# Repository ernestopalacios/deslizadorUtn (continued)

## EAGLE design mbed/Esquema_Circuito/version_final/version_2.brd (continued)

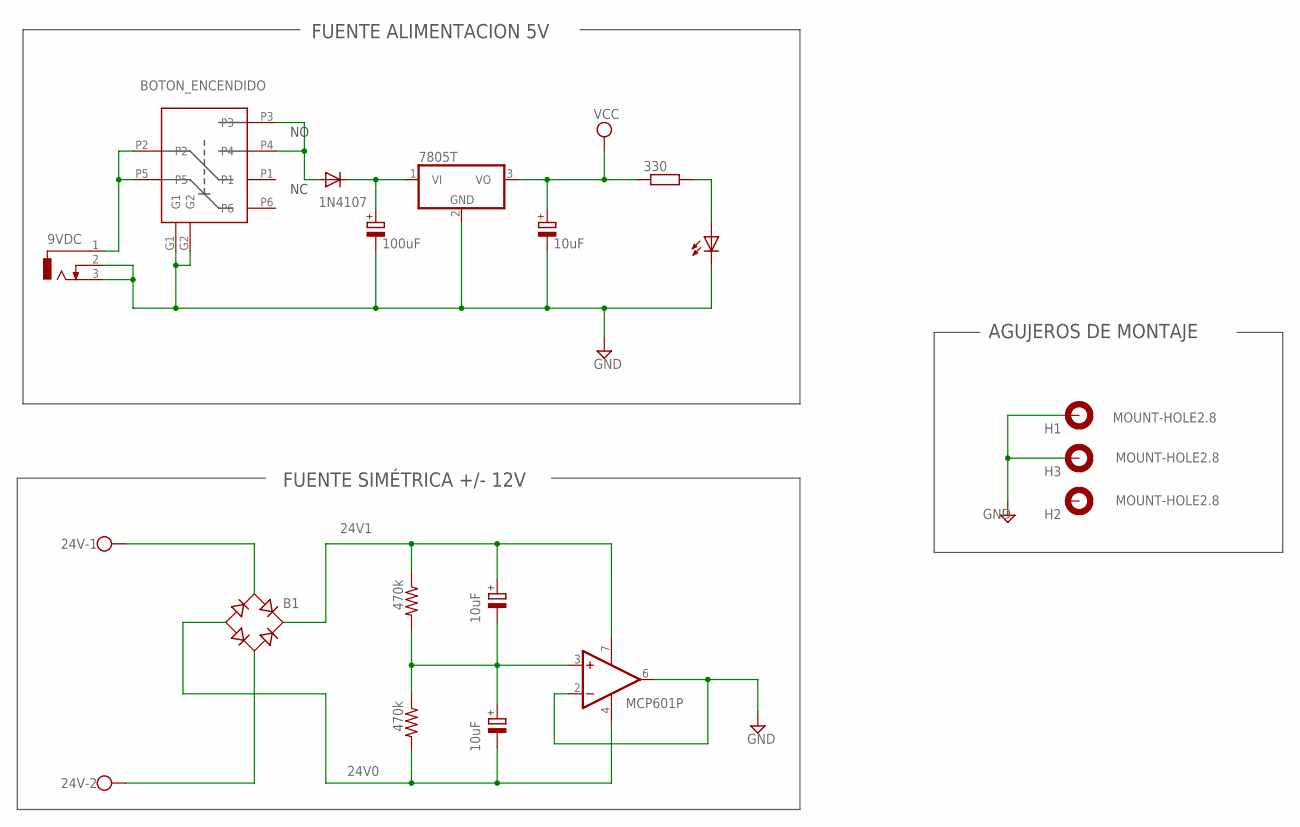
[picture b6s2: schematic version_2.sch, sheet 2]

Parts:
9VDC: DCJ0303
24V: W237-02P; W237-132
B1: RB1A
C1_9V: 100uF; TT5D7
C1_+24, C2_0V, C2_9V: 10uF; TT5D7
D1_INPUT: 1N4107; DO35-10
H1, H2, H3: MOUNT-HOLE2.8; 3,3-PAD
IC2: 7805T; TO220H
IC3: MCP601P; DIL08
ON/OFF: BOTON_ENCENDIDO; BOTON_ENCNEDIDO
POWER: LED3MM
PWR_LED_R: 330; 0204/7
R1_DIV, R2_DIV: 470k; 0207/10

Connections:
24V0: B1.-, C2_0V.-, IC3.4 (V-), R2_DIV.2; also elsewhere on the board
24V1: B1.+, C1_+24.+, IC3.7 (V+), R1_DIV.1; also elsewhere on the board
GND: 9VDC.2, 9VDC.3, C1_9V.-, C2_9V.-, H1.B3,3, H3.B3,3, IC2.2 (GND), IC3.2 (-IN), IC3.6 (OUT), ON/OFF.G1, ON/OFF.G2, POWER.K (C); also elsewhere on the board
unnamed: 24V.1, B1.AC1
unnamed: 24V.2, B1.AC2
unnamed: C1_+24.-, C2_0V.+, IC3.3 (+IN), R1_DIV.2, R2_DIV.1
unnamed: D1_INPUT.A, ON/OFF.P3, ON/OFF.P4
unnamed: 9VDC.1, ON/OFF.P2, ON/OFF.P5
unnamed: C1_9V.+, D1_INPUT.C, IC2.1 (VI)
unnamed: POWER.A, PWR_LED_R.2
VCC: C2_9V.+, IC2.3 (VO), PWR_LED_R.1; also elsewhere on the board

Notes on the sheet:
FUENTE ALIMENTACION 5V
FUENTE SIMÉTRICA +/- 12V
AGUJEROS DE MONTAJE

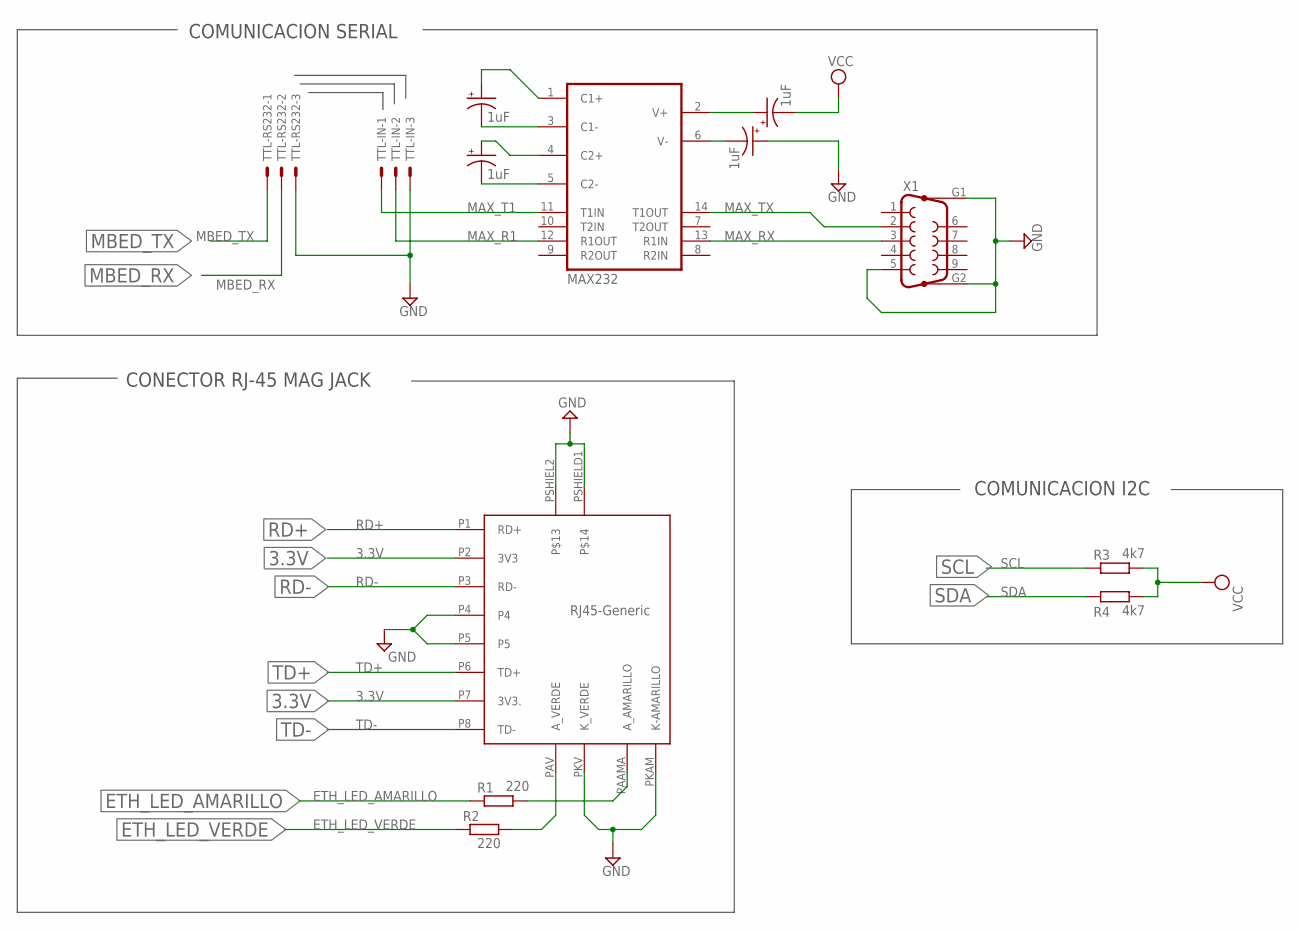
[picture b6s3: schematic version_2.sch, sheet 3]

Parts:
C1_MAX, C2_MAX, C3_MAX, C4_MAX: 1uF; E2,5-6E
IC1: MAX232; DIL16
R1, R2: 220; 0207/15
R3, R4: 4k7; 0204/7
TTL-IN: 22-23-2031
TTL-RS232: 22-23-2031
U$1: RJ-45-GENERIC; RJ45-GENERIC
X1: F09HP

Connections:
3.3V: U$1.P2 (3V3), U$1.P7 (3V3.); also elsewhere on the board
ETH_LED_AMARILLO: R1.1; also elsewhere on the board
ETH_LED_VERDE: R2.1; also elsewhere on the board
GND: C3_MAX.+, IC1.15 (GND), TTL-IN.3, TTL-RS232.3, U$1.P4, U$1.P5, U$1.PKAM (K-AMARILLO), U$1.PKV (K_VERDE), U$1.PSHIEL2, U$1.PSHIELD1, X1.5, X1.G1, X1.G2; also elsewhere on the board
MAX_R1: IC1.12 (R1OUT), TTL-IN.2
MAX_RX: IC1.13 (R1IN), X1.3; also elsewhere on the board
MAX_T1: IC1.11 (T1IN), TTL-IN.1
MAX_TX: IC1.14 (T1OUT), X1.2; also elsewhere on the board
MBED_RX: TTL-RS232.2; also elsewhere on the board
MBED_TX: TTL-RS232.1; also elsewhere on the board
unnamed: C1_MAX.+, IC1.1 (C1+)
unnamed: C1_MAX.-, IC1.3 (C1-)
unnamed: C2_MAX.-, IC1.5 (C2-)
unnamed: C2_MAX.+, IC1.4 (C2+)
unnamed: C4_MAX.+, IC1.2 (V+)
unnamed: C3_MAX.-, IC1.6 (V-)
unnamed: R1.2, U$1.PAAMA (A_AMARILLO)
unnamed: R2.2, U$1.PAV (A_VERDE)
RD+: U$1.P1 (RD+); also elsewhere on the board
RD-: U$1.P3 (RD-); also elsewhere on the board
SCL: R3.1; also elsewhere on the board
SDA: R4.1; also elsewhere on the board
TD+: U$1.P6 (TD+); also elsewhere on the board
TD-: U$1.P8 (TD-); also elsewhere on the board
VCC: C4_MAX.-, IC1.16 (VCC), R3.2, R4.2; also elsewhere on the board

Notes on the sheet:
CONECTOR RJ-45 MAG JACK
COMUNICACION SERIAL
COMUNICACION I2C

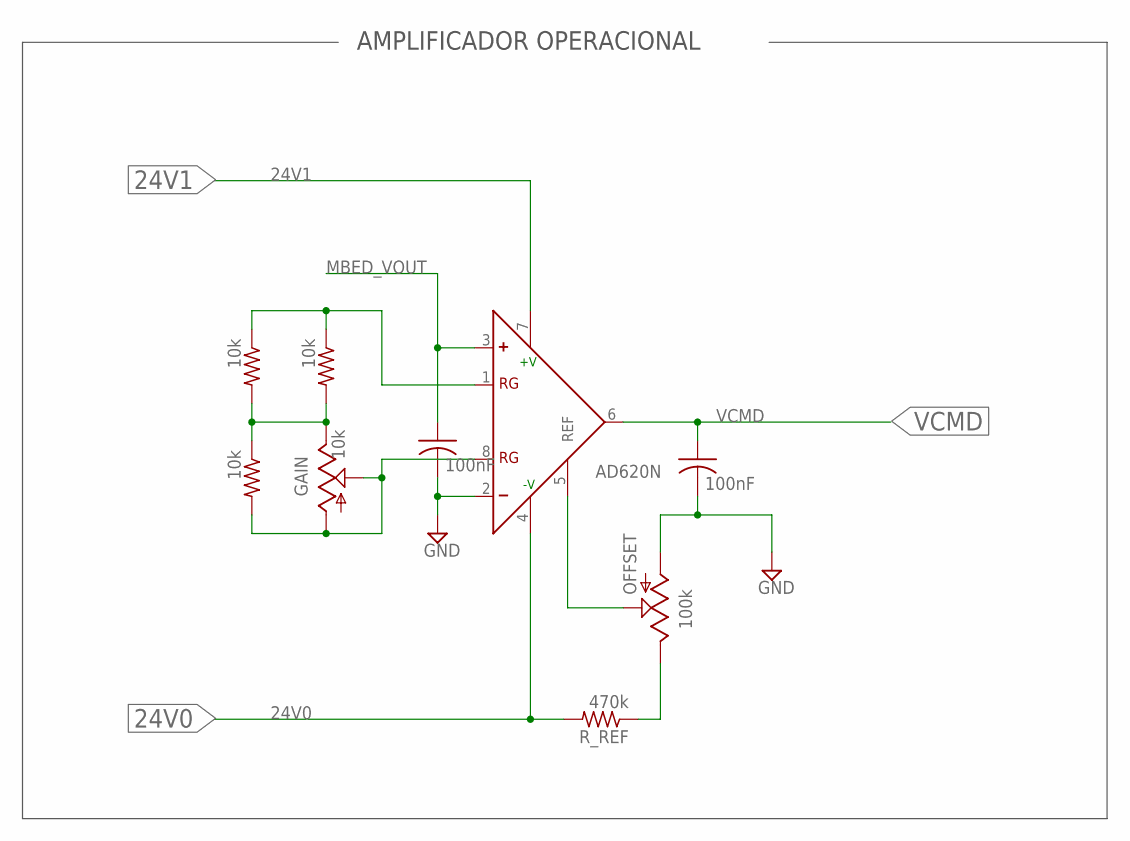
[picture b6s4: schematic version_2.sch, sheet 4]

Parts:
C3_AOUT, C5_AOUT: 100nF; C025-024X044
GAIN: 10k; RJ9W
IC4: AD620N; DIL08
OFFSET: 100k; RJ9W
R1_G, R2_G, R3_G: 10k; 0204/7
R_REF: 470k; 0204/7

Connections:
24V0: IC4.4 (-V), R_REF.2; also elsewhere on the board
24V1: IC4.7 (+V); also elsewhere on the board
GND: C3_AOUT.2, C5_AOUT.2, IC4.2 (-), OFFSET.A; also elsewhere on the board
MBED_VOUT: C5_AOUT.1, IC4.3 (+); also elsewhere on the board
unnamed: OFFSET.E, R_REF.1
unnamed: IC4.1 (RG), R1_G.1, R3_G.1
unnamed: GAIN.E, R1_G.2, R2_G.1, R3_G.2
unnamed: GAIN.A, GAIN.S, IC4.8 (RG), R2_G.2
unnamed: IC4.5 (REF), OFFSET.S
VCMD: C3_AOUT.1, IC4.6 (OUT); also elsewhere on the board

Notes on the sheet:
AMPLIFICADOR OPERACIONAL

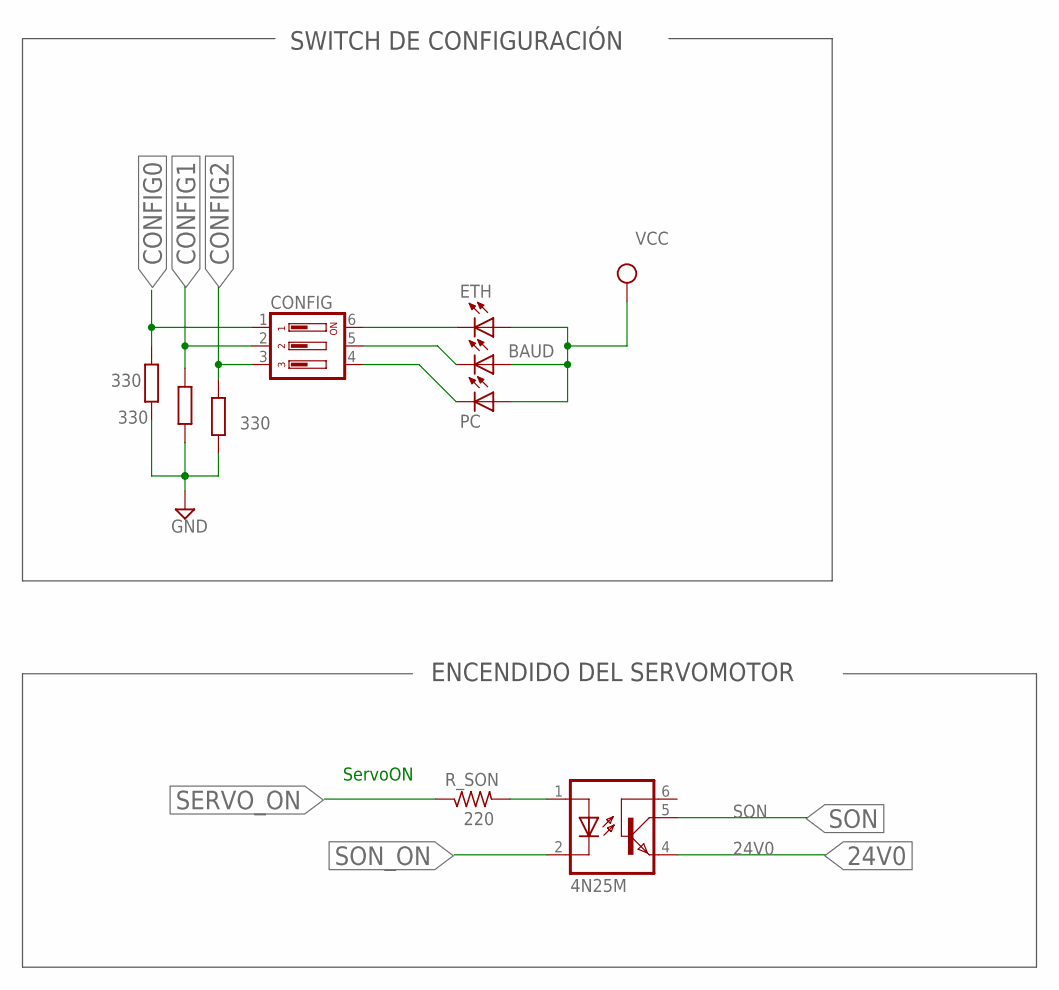
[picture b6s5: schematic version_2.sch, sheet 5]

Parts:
BAUD: LED3MM
CONFIG: DIP03YL
ETH: LED3MM
OK1: 4N25M; DIL06
PC: LED3MM
R13, R14, R15: 330; 0204/7
R_SON: 220; 0207/7

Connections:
24V0: OK1.4 (EMI); also elsewhere on the board
CONFIG0: CONFIG.1, R15.2; also elsewhere on the board
CONFIG1: CONFIG.2, R14.2; also elsewhere on the board
CONFIG2: CONFIG.3, R13.2; also elsewhere on the board
GND: R13.1, R14.1, R15.1; also elsewhere on the board
unnamed: OK1.1 (A), R_SON.2
unnamed: CONFIG.6, ETH.K (C)
unnamed: BAUD.K (C), CONFIG.5
unnamed: CONFIG.4, PC.K (C)
SERVO_ON: R_SON.1; also elsewhere on the board
SON: OK1.5 (COL); also elsewhere on the board
SON_ON: OK1.2 (C); also elsewhere on the board
VCC: BAUD.A, ETH.A, PC.A; also elsewhere on the board

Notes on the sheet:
ServoON
SWITCH DE CONFIGURACIÓN
ENCENDIDO DEL SERVOMOTOR

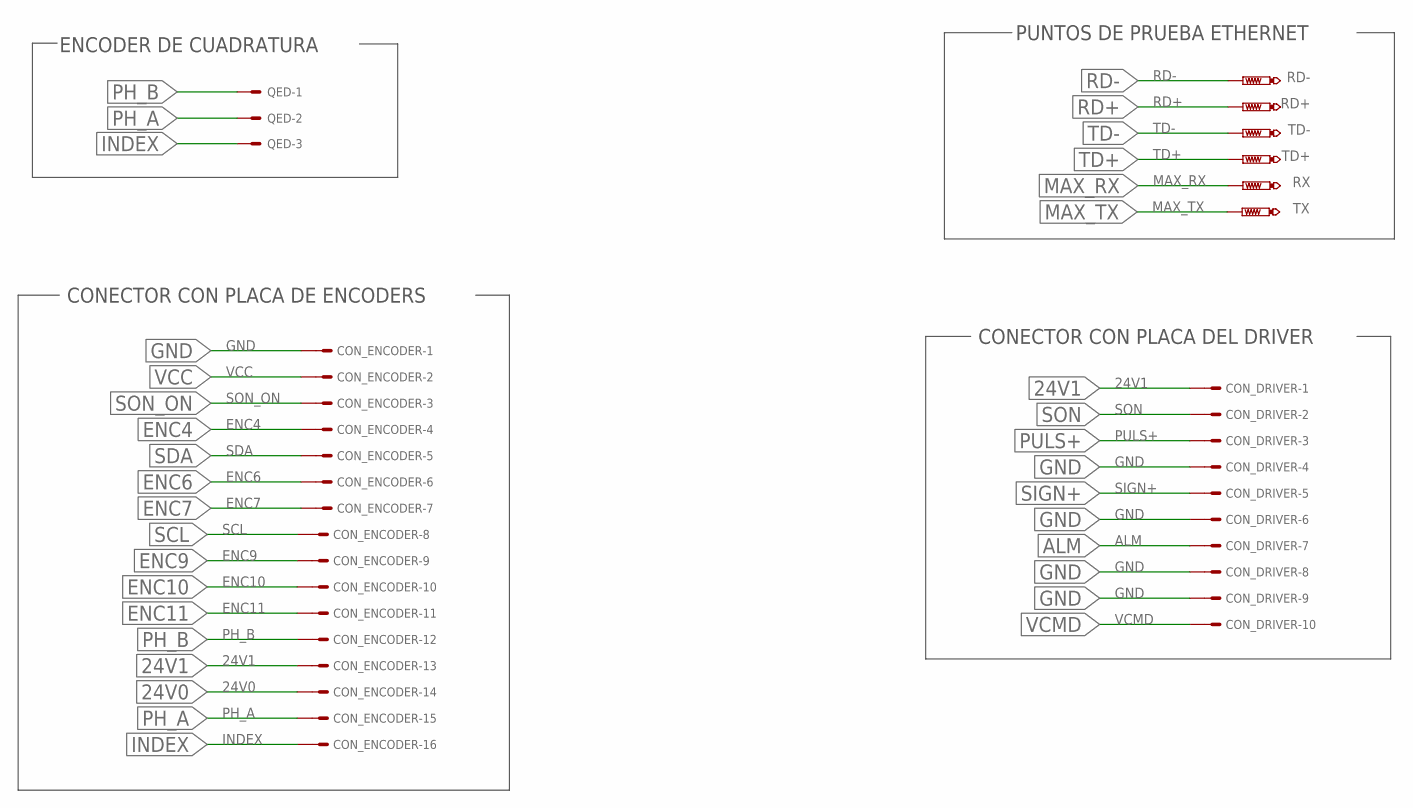
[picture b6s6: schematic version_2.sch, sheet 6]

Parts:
CON_DRIVER: 057-010-1
CON_ENCODER: 057-016-1
QED: 22-23-2031
RD+: PTR1PAD1-13Y; P1-13Y
RD-: PTR1PAD1-13Y; P1-13Y
RX: PTR1PAD1-13Y; P1-13Y
TD+: PTR1PAD1-13Y; P1-13Y
TD-: PTR1PAD1-13Y; P1-13Y
TX: PTR1PAD1-13Y; P1-13Y

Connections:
24V0: CON_ENCODER.14; also elsewhere on the board
24V1: CON_DRIVER.1, CON_ENCODER.13; also elsewhere on the board
ALM: CON_DRIVER.7; also elsewhere on the board
ENC4: CON_ENCODER.4; also elsewhere on the board
ENC6: CON_ENCODER.6; also elsewhere on the board
ENC7: CON_ENCODER.7; also elsewhere on the board
ENC9: CON_ENCODER.9; also elsewhere on the board
ENC10: CON_ENCODER.10
ENC11: CON_ENCODER.11
GND: CON_DRIVER.4, CON_DRIVER.6, CON_DRIVER.8, CON_DRIVER.9, CON_ENCODER.1; also elsewhere on the board
INDEX: CON_ENCODER.16, QED.3
MAX_RX: RX.TP; also elsewhere on the board
MAX_TX: TX.TP; also elsewhere on the board
PH_A: CON_ENCODER.15, QED.2
PH_B: CON_ENCODER.12, QED.1
PULS+: CON_DRIVER.3; also elsewhere on the board
RD+: RD+.TP; also elsewhere on the board
RD-: RD-.TP; also elsewhere on the board
SCL: CON_ENCODER.8; also elsewhere on the board
SDA: CON_ENCODER.5; also elsewhere on the board
SIGN+: CON_DRIVER.5; also elsewhere on the board
SON: CON_DRIVER.2; also elsewhere on the board
SON_ON: CON_ENCODER.3; also elsewhere on the board
TD+: TD+.TP; also elsewhere on the board
TD-: TD-.TP; also elsewhere on the board
VCC: CON_ENCODER.2; also elsewhere on the board
VCMD: CON_DRIVER.10; also elsewhere on the board

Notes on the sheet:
ENCODER DE CUADRATURA
PUNTOS DE PRUEBA ETHERNET
CONECTOR CON PLACA DE ENCODERS
CONECTOR CON PLACA DEL DRIVER

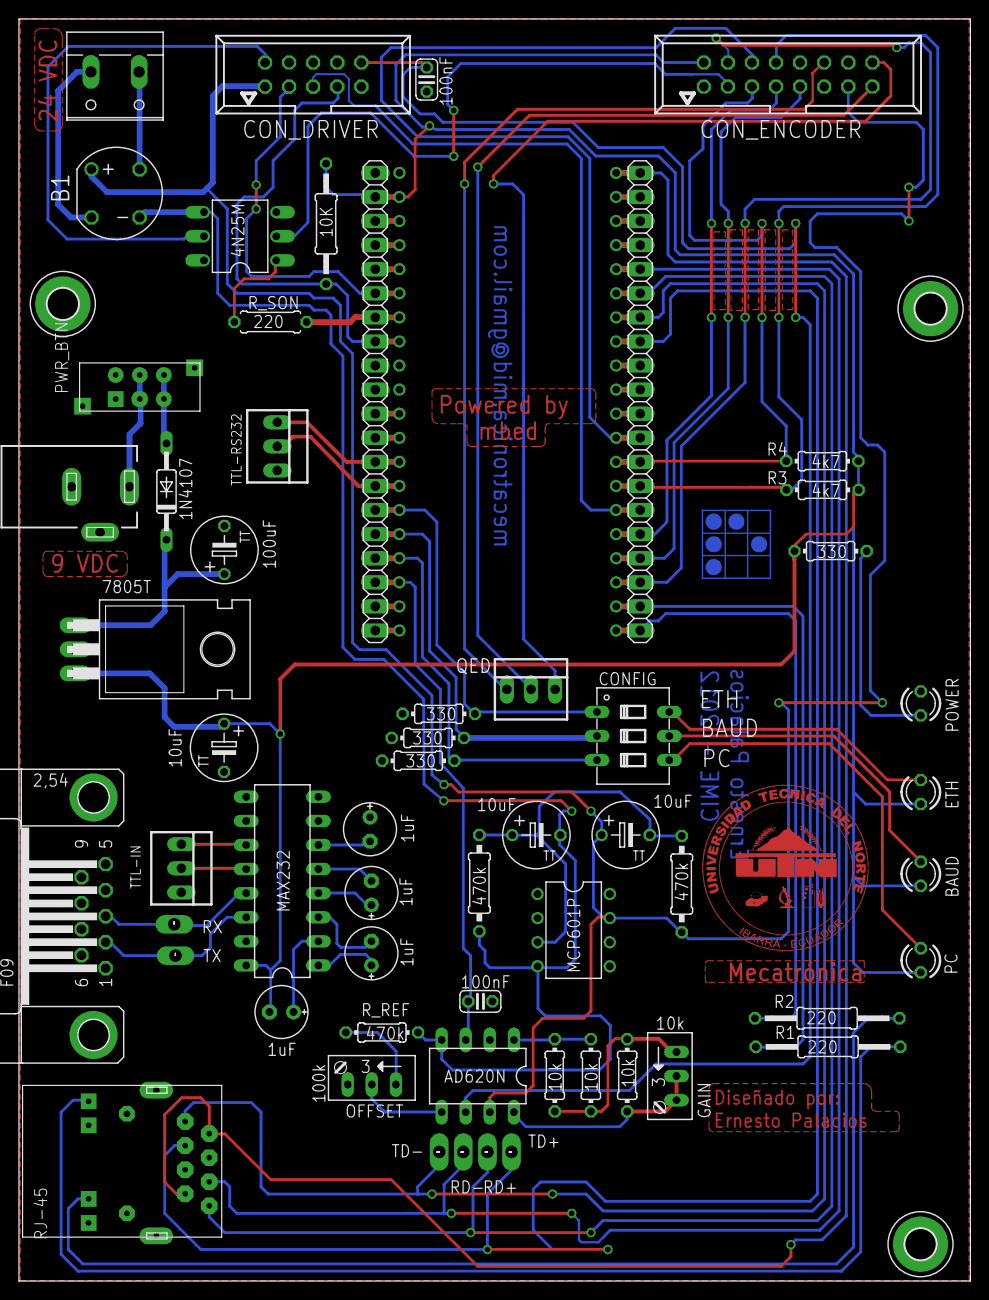
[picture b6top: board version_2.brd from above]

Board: 2 copper layers, 100.3 x 133.1 mm, 62 parts (0 on the bottom side), 76 nets.

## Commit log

2014-10-08 Añadidos archivos base
2014-11-22 Removidos archivos innecesarios
2014-11-22 Se separo el archivo TrabajodeGrado en varios archivos y un PDF
2014-11-23 Añadido archivo de tesis y removido .ini
2015-01-25 Update README.md
    Enlace al manual de ayuda
